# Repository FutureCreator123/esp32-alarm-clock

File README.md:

# esp32-alarm-clock
This project is proudly present to you by Yuvan. Want to build your own alarm clock? Or looking for open-source hardware you can customize to your needs? This project is the perfect place to start. It provides a flexible, open design for building and modifying your own alarm clock—whether you just want the hardware or a smarter clock.
If you found this project helpful or interesting, please don't forget to star and like it!

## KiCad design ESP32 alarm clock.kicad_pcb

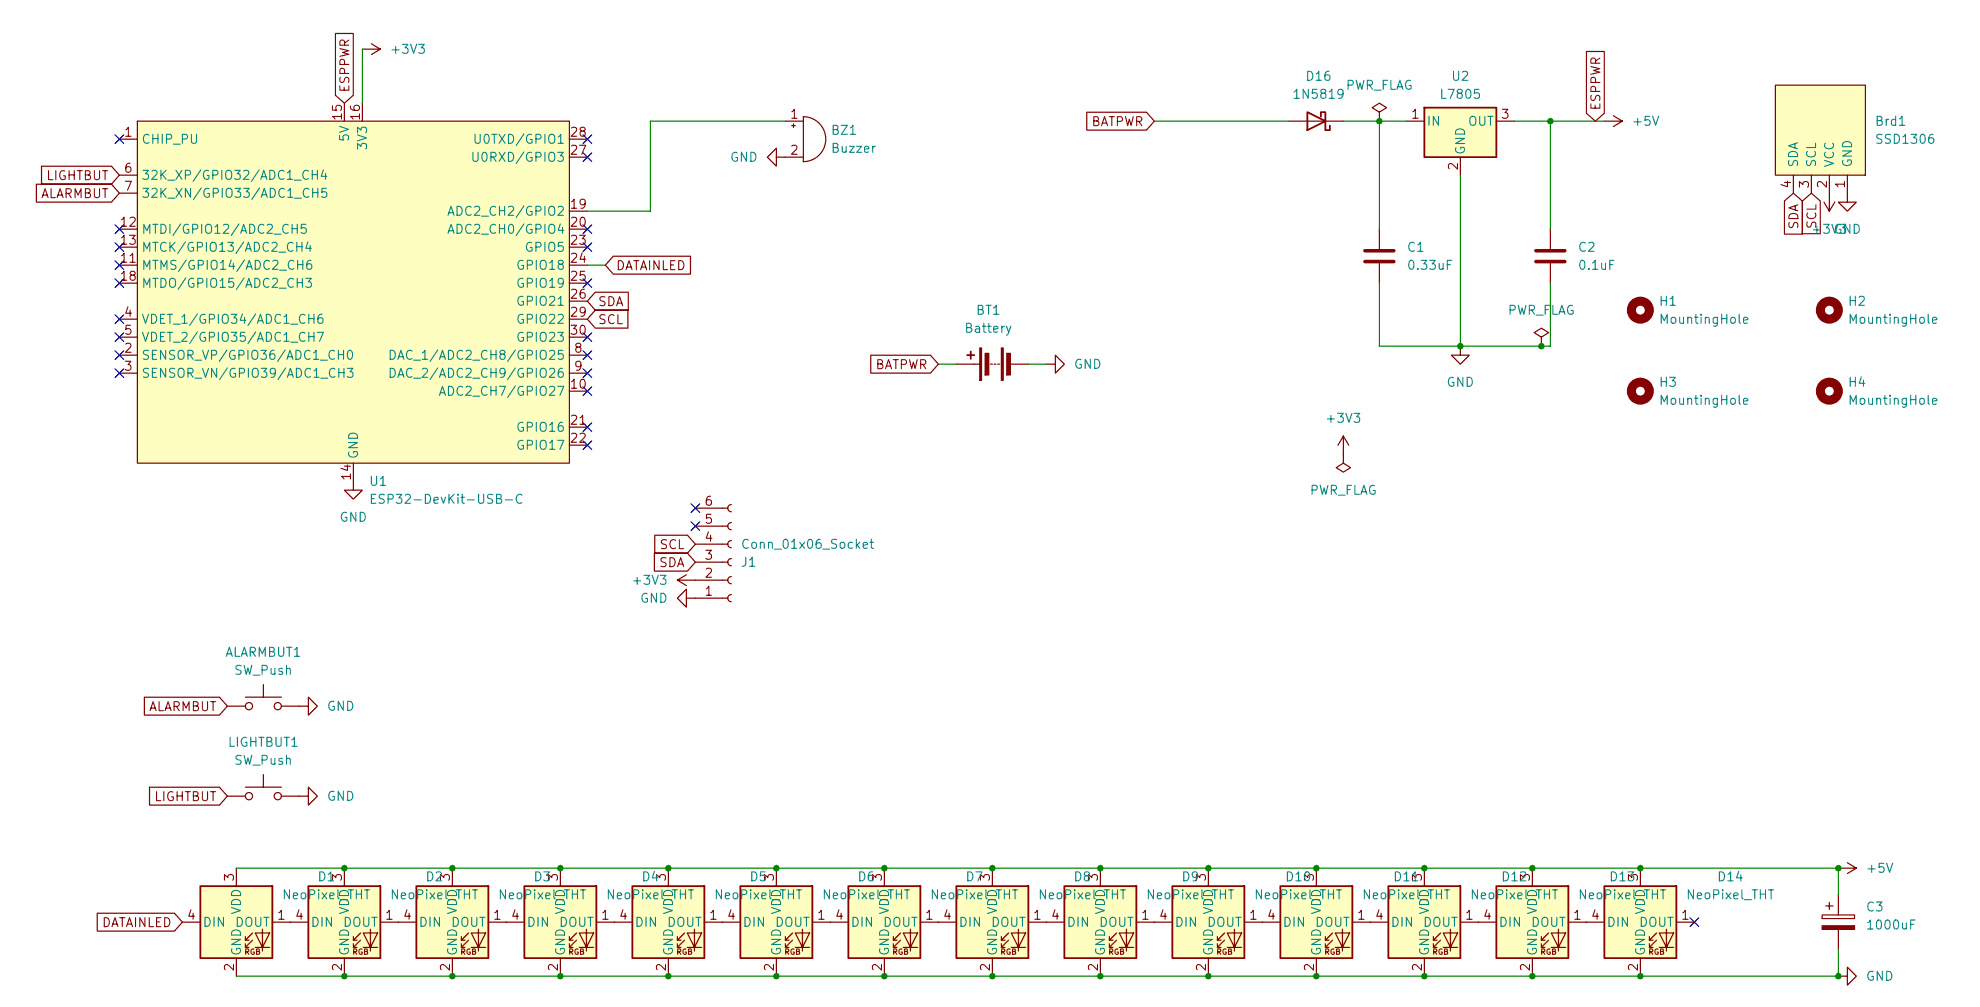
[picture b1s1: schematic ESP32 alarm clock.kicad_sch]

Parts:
ALARMBUT1: SW_Push; SW_PUSH_6mm
BT1: Battery; TerminalBlock_Phoenix_MKDS-1,5-2-5.08_1x02_P5.08mm_Horizont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
BZ1: Buzzer; Buzzer_D14mm_H7mm_P10mm
Brd1: SSD1306; 128x64OLED
C1: 0.33uF; C_Disc_D5.0mm_W2.5mm_P2.50mm
C2: 0.1uF; C_Disc_D5.0mm_W2.5mm_P2.50mm
C3: 1000uF; CP_Radial_D10.0mm_P5.00mm
D1, D2, D3, D4, D5, D6, D7, D8, D9, D10, D11, D12, D13, D14: NeoPixel_THT; my_neopixel_THT
D16: 1N5819; D_DO-41_SOD81_P10.16mm_Horizontal
H1, H2, H3, H4: MountingHole; MountingHole_3.2mm_M3_DIN965_Pad
J1: Conn_01x06_Socket; PinSocket_1x06_P2.00mm_Horizontal
LIGHTBUT1: SW_Push; SW_PUSH_6mm
U1: ESP32-DevKit-USB-C
U2: L7805; TO-220F-3_Horizontal_TabDown

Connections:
+3V3: Brd1.2 (VCC), J1.2, U1.16 (3V3)
ALARMBUT: ALARMBUT1.1, U1.7 (32K_XN/GPIO33/ADC1_CH5)
BATPWR: BT1.1 (+), D16.2 (A)
DATAINLED: D1.4 (DIN), U1.24 (GPIO18)
ESPPWR: C2.1, C3.1, D1.3 (VDD), D2.3 (VDD), D3.3 (VDD), D4.3 (VDD), D5.3 (VDD), D6.3 (VDD), D7.3 (VDD), D8.3 (VDD), D9.3 (VDD), D10.3 (VDD), D11.3 (VDD), D12.3 (VDD), D13.3 (VDD), D14.3 (VDD), U1.15 (5V), U2.3 (OUT)
GND: ALARMBUT1.2, BT1.2 (-), BZ1.2 (-), Brd1.1 (GND), C1.2, C2.2, C3.2, D1.2 (GND), D2.2 (GND), D3.2 (GND), D4.2 (GND), D5.2 (GND), D6.2 (GND), D7.2 (GND), D8.2 (GND), D9.2 (GND), D10.2 (GND), D11.2 (GND), D12.2 (GND), D13.2 (GND), D14.2 (GND), J1.1, LIGHTBUT1.2, U1.14 (GND), U1.17 (GND), U2.2 (GND)
LIGHTBUT: LIGHTBUT1.1, U1.6 (32K_XP/GPIO32/ADC1_CH4)
unnamed: BZ1.1 (+), U1.19 (ADC2_CH2/GPIO2)
unnamed: D1.1 (DOUT), D2.4 (DIN)
unnamed: D2.1 (DOUT), D3.4 (DIN)
unnamed: D3.1 (DOUT), D4.4 (DIN)
unnamed: D4.1 (DOUT), D5.4 (DIN)
unnamed: D5.1 (DOUT), D6.4 (DIN)
unnamed: D6.1 (DOUT), D7.4 (DIN)
unnamed: D7.1 (DOUT), D8.4 (DIN)
unnamed: D8.1 (DOUT), D9.4 (DIN)
unnamed: D9.1 (DOUT), D10.4 (DIN)
unnamed: D10.1 (DOUT), D11.4 (DIN)
unnamed: D11.1 (DOUT), D12.4 (DIN)
unnamed: D12.1 (DOUT), D13.4 (DIN)
unnamed: D13.1 (DOUT), D14.4 (DIN)
unnamed: C1.1, D16.1 (K), U2.1 (IN)
SCL: Brd1.3 (SCL), J1.4, U1.29 (GPIO22)
SDA: Brd1.4 (SDA), J1.3, U1.26 (GPIO21)

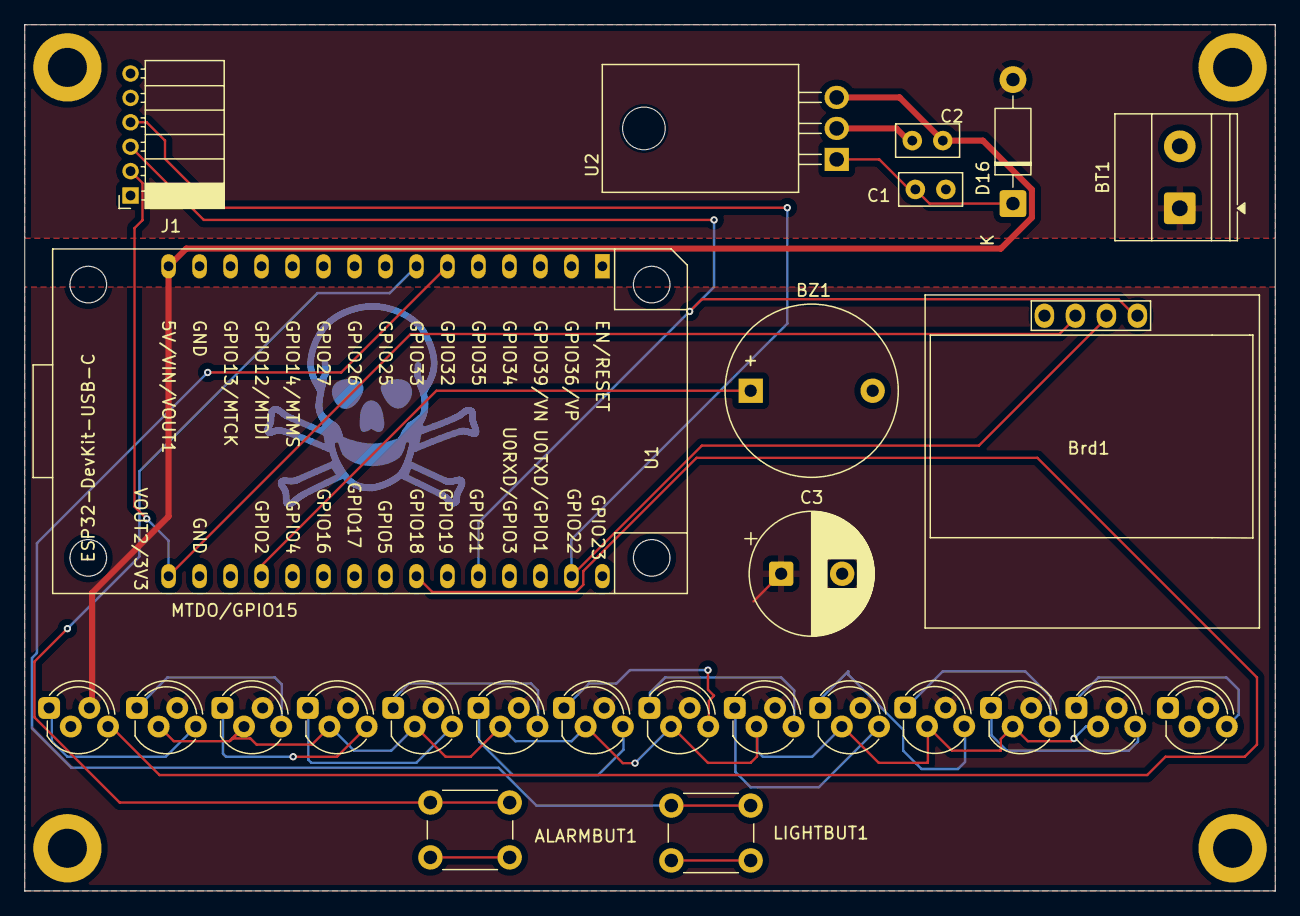
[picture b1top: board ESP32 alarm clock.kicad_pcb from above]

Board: 2 copper layers, 102.4 x 71.0 mm, 30 parts (0 on the bottom side), 24 nets.

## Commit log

2026-03-14 Moved to esp32-alarm-clock-main folder
